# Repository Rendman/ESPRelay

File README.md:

# ESP8266 2-Channel Relay
---
This project was originally designed to act a as wifi enabled IoT garage door opener. It has two relay channels and two sensor channels. 

This hardware is largely a rip off of standard "Arduino" modules that you can find on eBay and other sources. It's really nothing special. It does proivde a higher degree of integration as you can mount a NodeMCU directly to the PCB. 

I've tested this with the TASMOTA software and it seems to work pretty well. 

Here is the TASMOTA Config for the module. Any kind of Commands or Backlog things are left to the user.

GPIO -> Function
---
GPIO4 -> Relay2  
GPIO5 -> Relay1  
GPIO12 -> Switch2  
GPIO14 -> Switch1  

This project also includes FreeCAD files for a 3D printable box for the device. I used the following as the magnetic sensor, but any other one would work just fine:

[Seco-Larm Overhead Door Sensor](https://www.amazon.com/SECO-LARM-SM-4201-LQ-TRACK-MOUNT-OVERHEAD/dp/B011OXPZ7Y/ref=sr_1_16?crid=1GI1UTF3R9V3U&dchild=1&keywords=seco-larm+sm-226lq+overhead+door-mount+n.o.+magnetic+contact&qid=1628387442&sprefix=seco-larm+overhead+doo%2Caps%2C196&sr=8-16)

Here are a few pictures of the device and the sensor

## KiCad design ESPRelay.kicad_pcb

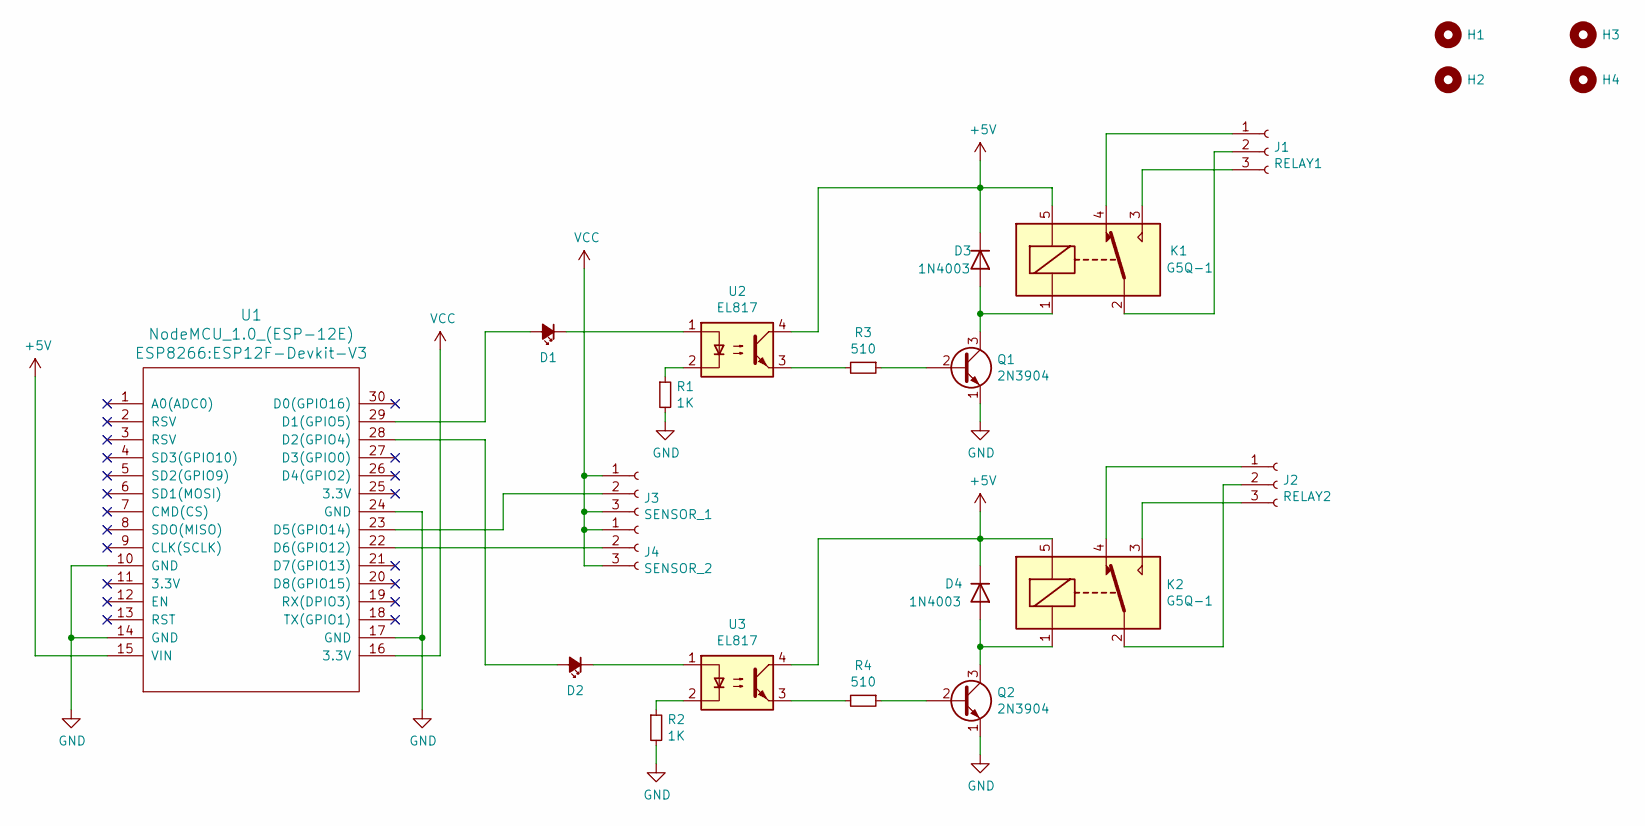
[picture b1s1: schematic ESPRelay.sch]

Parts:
D1, D2: LED_Small_ALT; LED_D5.0mm
D3, D4: 1N4003; D_DO-41_SOD81_P10.16mm_Horizontal
H1, H2, H3, H4: MountingHole; MountingHole_3.2mm_M3
J1: RELAY1; 5442251
J2: RELAY2; 5442251
J3: SENSOR_1; TerminalBlock_TE_282834-3_1x03_P2.54mm_Horizontal
J4: SENSOR_2; TerminalBlock_TE_282834-3_1x03_P2.54mm_Horizontal
K1, K2: G5Q-1; Relay_SPDT_Omron-G5Q-1
Q1, Q2: 2N3904; TO-92_Inline
R1, R2: 1K; R_Axial_DIN0204_L3.6mm_D1.6mm_P5.08mm_Horizontal
R3, R4: 510; R_Axial_DIN0204_L3.6mm_D1.6mm_P5.08mm_Horizontal
U1: NodeMCU_1.0_(ESP-12E); ESP12F-Devkit-V3
U2, U3: EL817; DIP-4_W7.62mm

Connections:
+5V: D3.1 (K), D4.1 (K), K1.5, K2.5, U1.15 (VIN), U2.4, U3.4
GND: Q1.1 (E), Q2.1 (E), R1.2, R2.2, U1.10 (GND), U1.14 (GND), U1.17 (GND), U1.24 (GND)
unnamed: D1.1 (K), U2.1
unnamed: D1.2 (A), U1.29 (D1(GPIO5))
unnamed: D2.1 (K), U3.1
unnamed: D2.2 (A), U1.28 (D2(GPIO4))
unnamed: D3.2 (A), K1.1, Q1.3 (C)
unnamed: D4.2 (A), K2.1, Q2.3 (C)
unnamed: J1.1, K1.4
unnamed: J1.2, K1.2
unnamed: J1.3, K1.3
unnamed: J2.1, K2.4
unnamed: J2.2, K2.2
unnamed: J2.3, K2.3
unnamed: J3.2, U1.23 (D5(GPIO14))
unnamed: J4.2, U1.22 (D6(GPIO12))
unnamed: Q1.2 (B), R3.1
unnamed: Q2.2 (B), R4.1
unnamed: R1.1, U2.2
unnamed: R2.1, U3.2
unnamed: R3.2, U2.3
unnamed: R4.2, U3.3
VCC: J3.1, J3.3, J4.1, J4.3, U1.16 (3.3V)

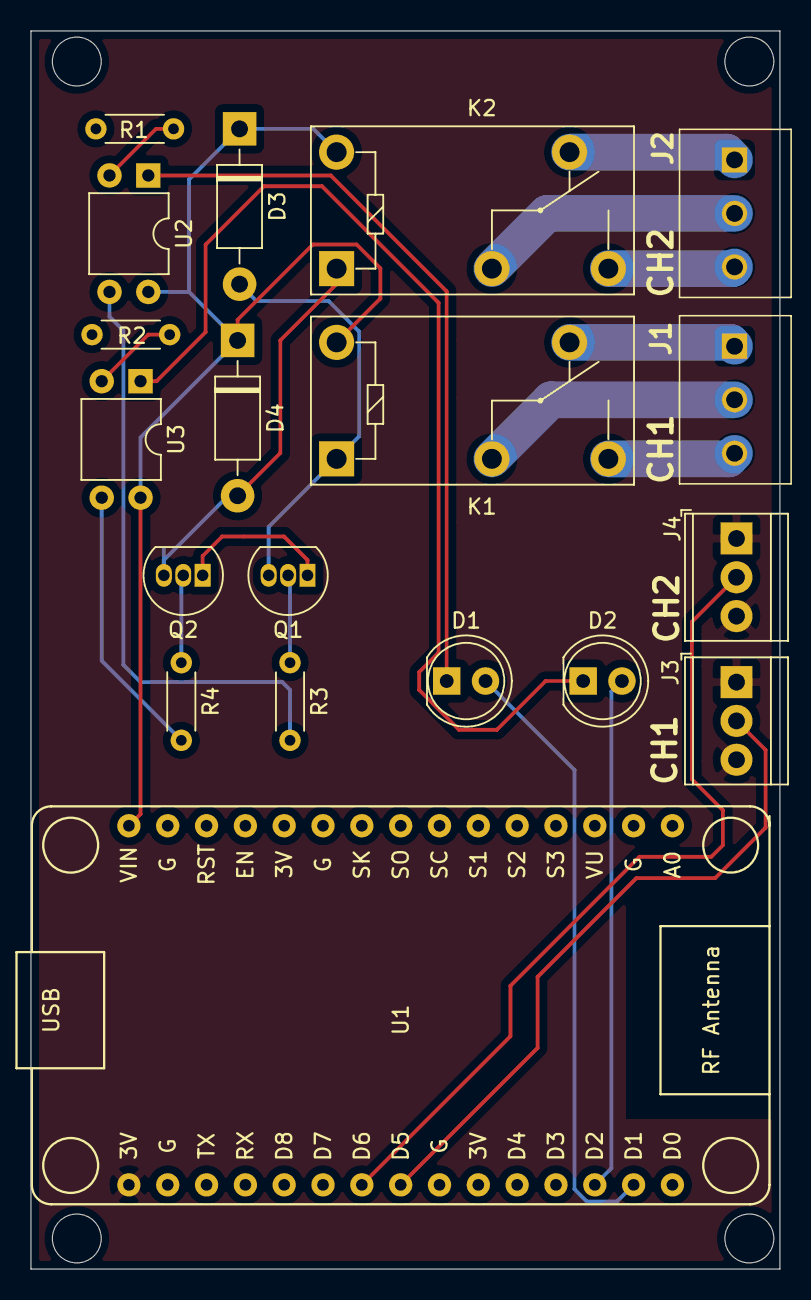
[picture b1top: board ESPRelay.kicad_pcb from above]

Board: 2 copper layers, 49.0 x 81.0 mm, 23 parts (0 on the bottom side), 23 nets.

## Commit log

2021-02-06 Initial Commit of Finished files
2021-02-07 Removed offensive message on silkscreen
2021-02-13 Slight cosmetic tweaks to manufacturing data and PCB silkscreen
2021-02-28 Fixed misconnected sensor inputs
2021-08-08 Fix error with relay connections to NodeMCU. Include README.md and git ignore file.
2021-08-08 .gitingnore now .gitignore... duh
2021-08-08 Removed generated files
2021-08-08 Deleted files that are no longer required
